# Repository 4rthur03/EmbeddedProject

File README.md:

# EmbeddedProject
Small embedded project to practice making firmware using the BeagleBone Black

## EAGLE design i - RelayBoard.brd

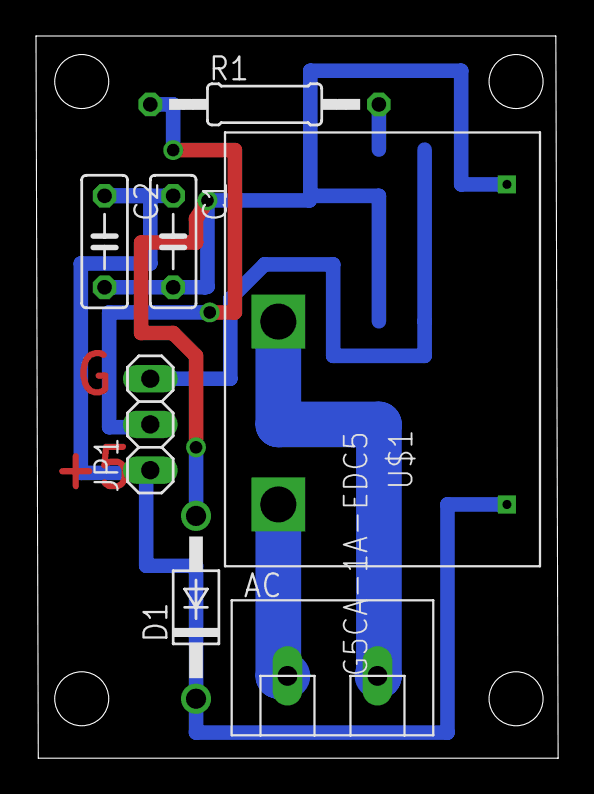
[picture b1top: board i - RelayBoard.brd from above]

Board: 2 copper layers, 29.0 x 40.1 mm, 8 parts (1 on the bottom side), 7 nets.

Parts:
AC: TERMINAL2; TERM2
C1: 0.001u; C050-025X075
C2: 0.1u; C050-025X075
D1: 1N4004; DO41-10
JP1: 1X03
OK6: LTV816S; DIL4-SMD
R1: 60; 0207/12
U$1: G5CA-1A-EDC5

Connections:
+5V: C1.1, C2.1, D1.C, JP1.1, U$1.P$1
GND: JP1.3, OK6.2, OK6.3
GPIO0_66: JP1.2, R1.1
unnamed: AC.2, U$1.P$4
unnamed: AC.1, U$1.P$3
unnamed: C1.2, C2.2, D1.A, OK6.4, U$1.P$2
unnamed: OK6.1, R1.2

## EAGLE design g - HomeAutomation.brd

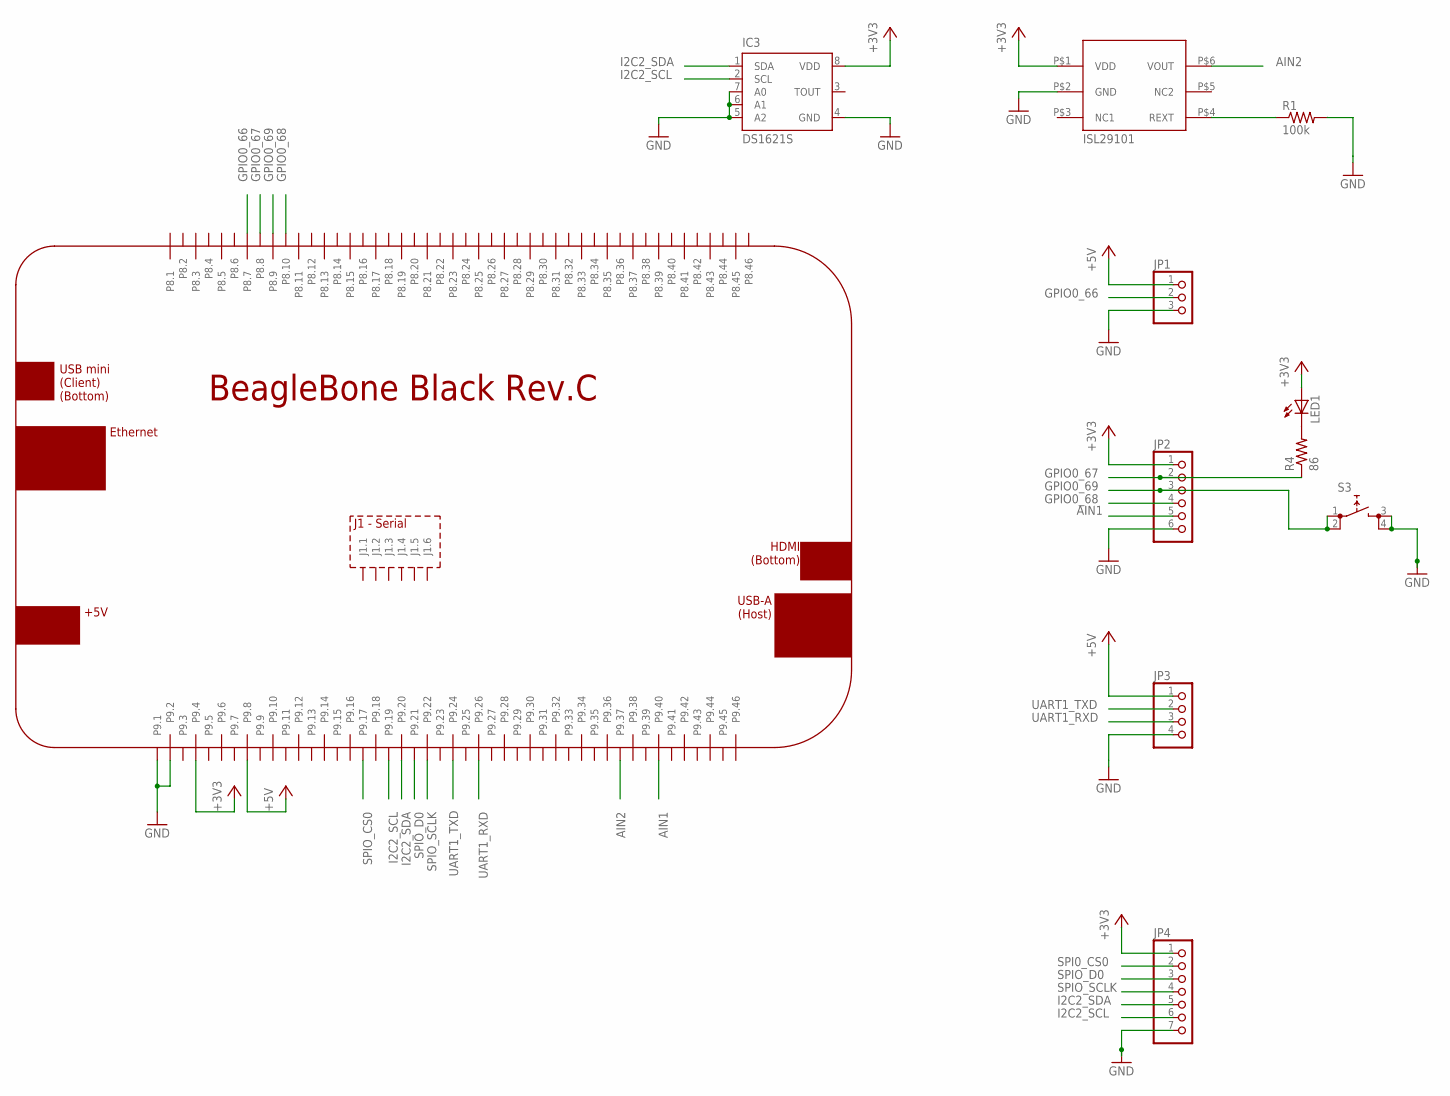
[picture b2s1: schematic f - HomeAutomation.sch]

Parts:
IC3: DS1621S; SO08
JP1: PINHD-1X3; 1X03
JP2: PINHD-1X6; 1X06
JP3: PINHD-1X4; 1X04
JP4: PINHD-1X7; 1X07
LED1: LED3MM
PCB1: BEAGLEBONE_BLACK_CAPE
R1: 100k; R0805
R4: 86; R0805
S3: PUSHBUTTON; TL1105SP
U$1: ISL29101; ODFN6

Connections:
+3V3: IC3.8 (VDD), JP2.1, JP4.1, LED1.A, PCB1.P9.4, U$1.P$1 (VDD)
+5V: JP1.1, JP3.1, PCB1.P9.8
AIN1: JP2.5, PCB1.P9.40
AIN2: PCB1.P9.37, U$1.P$6 (VOUT)
GND: IC3.4 (GND), IC3.5 (A2), IC3.6 (A1), IC3.7 (A0), JP1.3, JP2.6, JP3.4, JP4.7, PCB1.P9.1, PCB1.P9.2, R1.2, S3.3 (1), S3.4 (1), U$1.P$2 (GND)
GPIO0_66: JP1.2, PCB1.P8.7
GPIO0_67: JP2.2, PCB1.P8.8, R4.1
GPIO0_68: JP2.4, PCB1.P8.10
GPIO0_69: JP2.3, PCB1.P8.9, S3.1 (0), S3.2 (0)
I2C2_SCL: IC3.2 (SCL), JP4.6, PCB1.P9.19
I2C2_SDA: IC3.1 (SDA), JP4.5, PCB1.P9.20
unnamed: R1.1, U$1.P$4 (REXT)
unnamed: LED1.K (C), R4.2
SPI0_CS0: JP4.2
SPIO_CS0: PCB1.P9.17
SPIO_D0: JP4.3, PCB1.P9.21
SPIO_SCLK: JP4.4, PCB1.P9.22
UART1_RXD: JP3.3, PCB1.P9.26
UART1_TXD: JP3.2, PCB1.P9.24

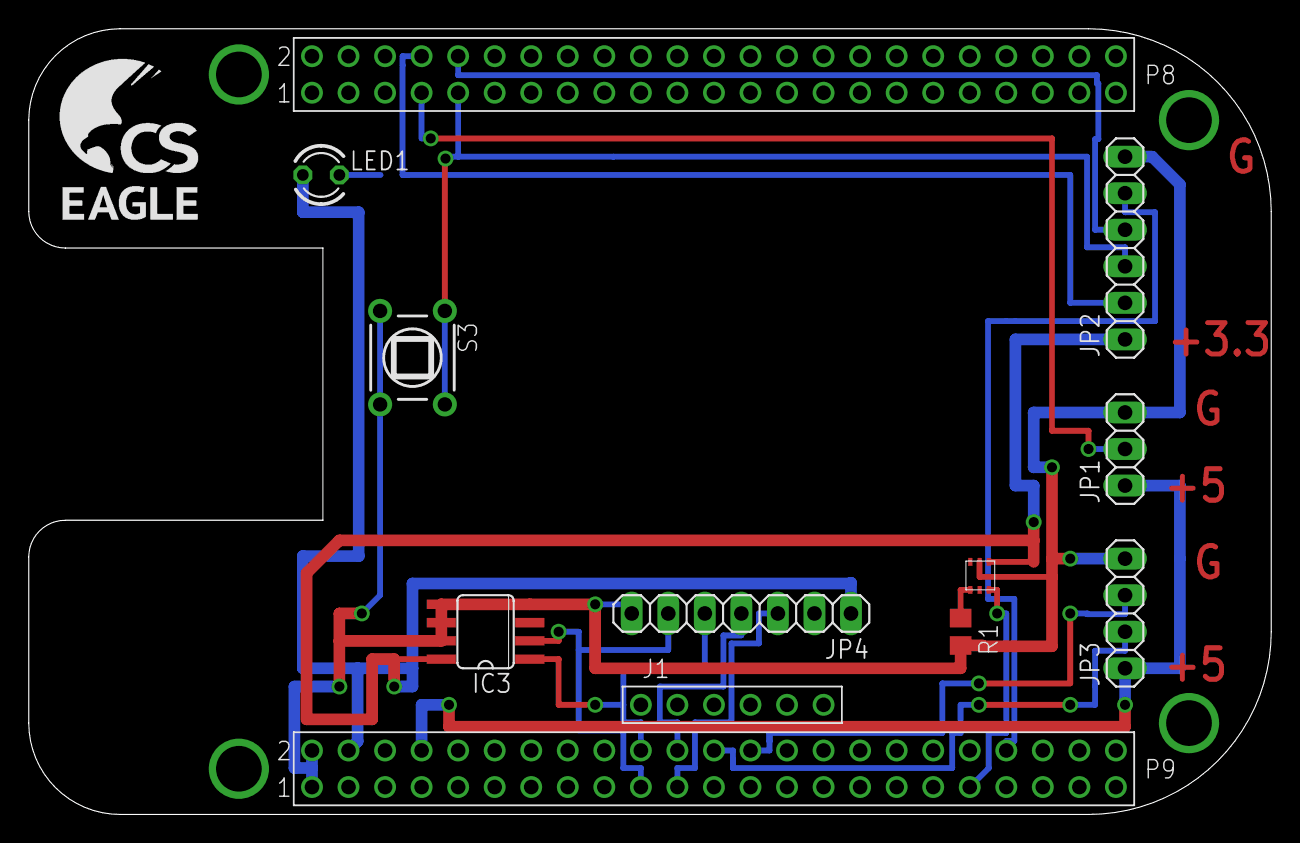
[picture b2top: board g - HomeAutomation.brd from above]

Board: 2 copper layers, 86.4 x 54.6 mm, 11 parts (1 on the bottom side), 17 nets.

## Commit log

2019-10-17 Some project
2019-10-17 Make some changes
